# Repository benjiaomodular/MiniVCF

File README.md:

# MiniVCF

This is a diode-ladder voltage controlled low pass filter based on [Moritz Klein's diode ladder tutorial series](https://www.youtube.com/watch?v=jvNNgUl3al0).

More info on my website:  [https://benjiaomodular.com/post/2022-03-11-mini-vcf/](https://benjiaomodular.com/post/2022-03-11-mini-vcf/)

## Versions

### v1.1 - Quick fixes (Unverified)
- Fixed orientation of Cutoff and Post-LPF knobs.
- Updated toggle switch footprint to a bit more space.
- Swapped clipping LED positions. Positive clipping now at the top row.
- Added missing labels for OpAmps, adjusted some unreadable labels.

### v1.0 - Initial release
This is the first release of the module. I got it to work, but has a couple of issues.

#### Issues Encountered
- Cutoff and Post-LPF knobs are wired the opposite way.
- Holes for the toggle switch a bit too tight.

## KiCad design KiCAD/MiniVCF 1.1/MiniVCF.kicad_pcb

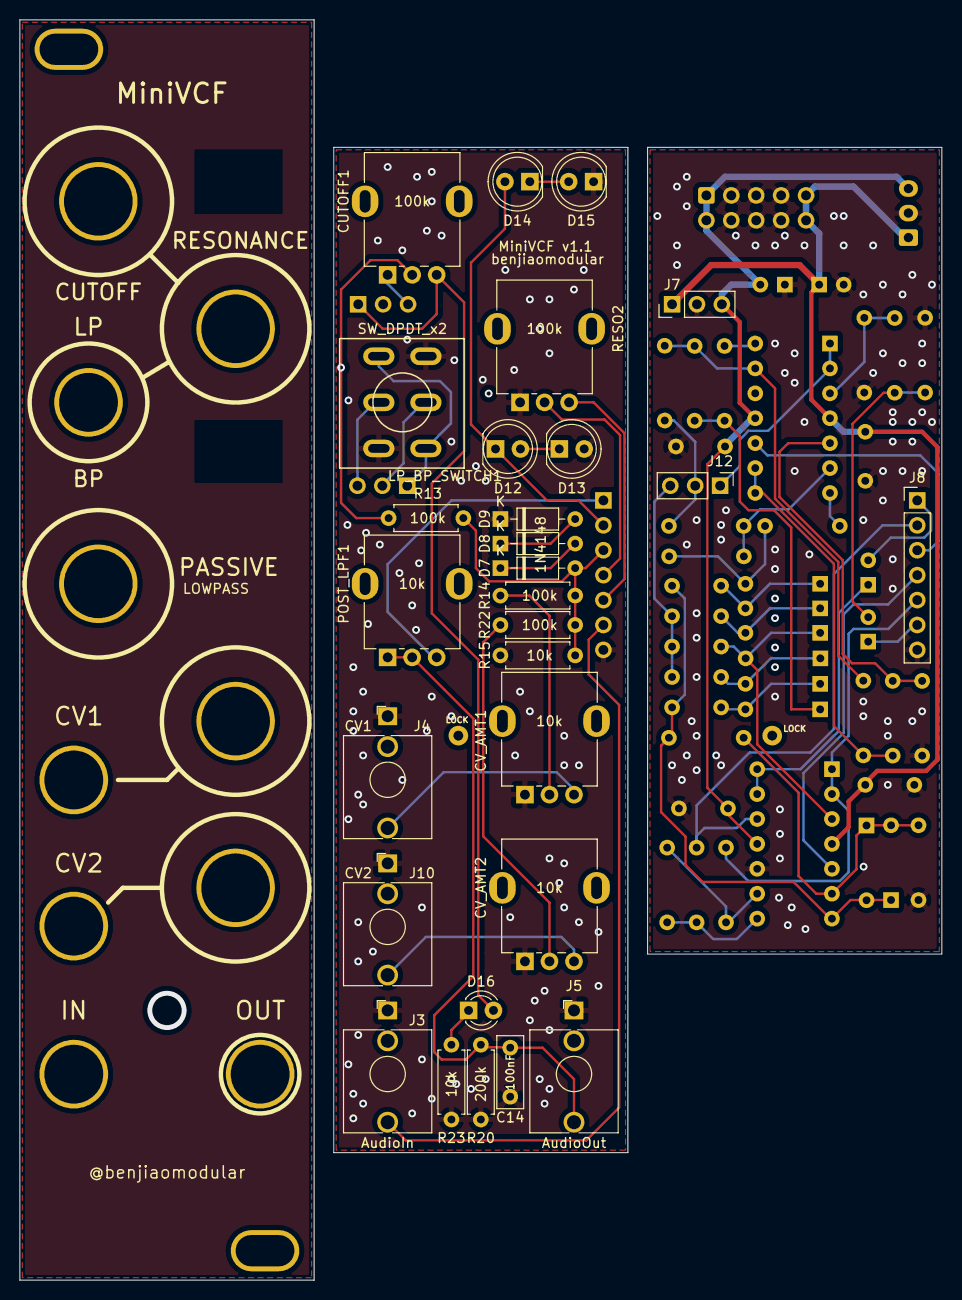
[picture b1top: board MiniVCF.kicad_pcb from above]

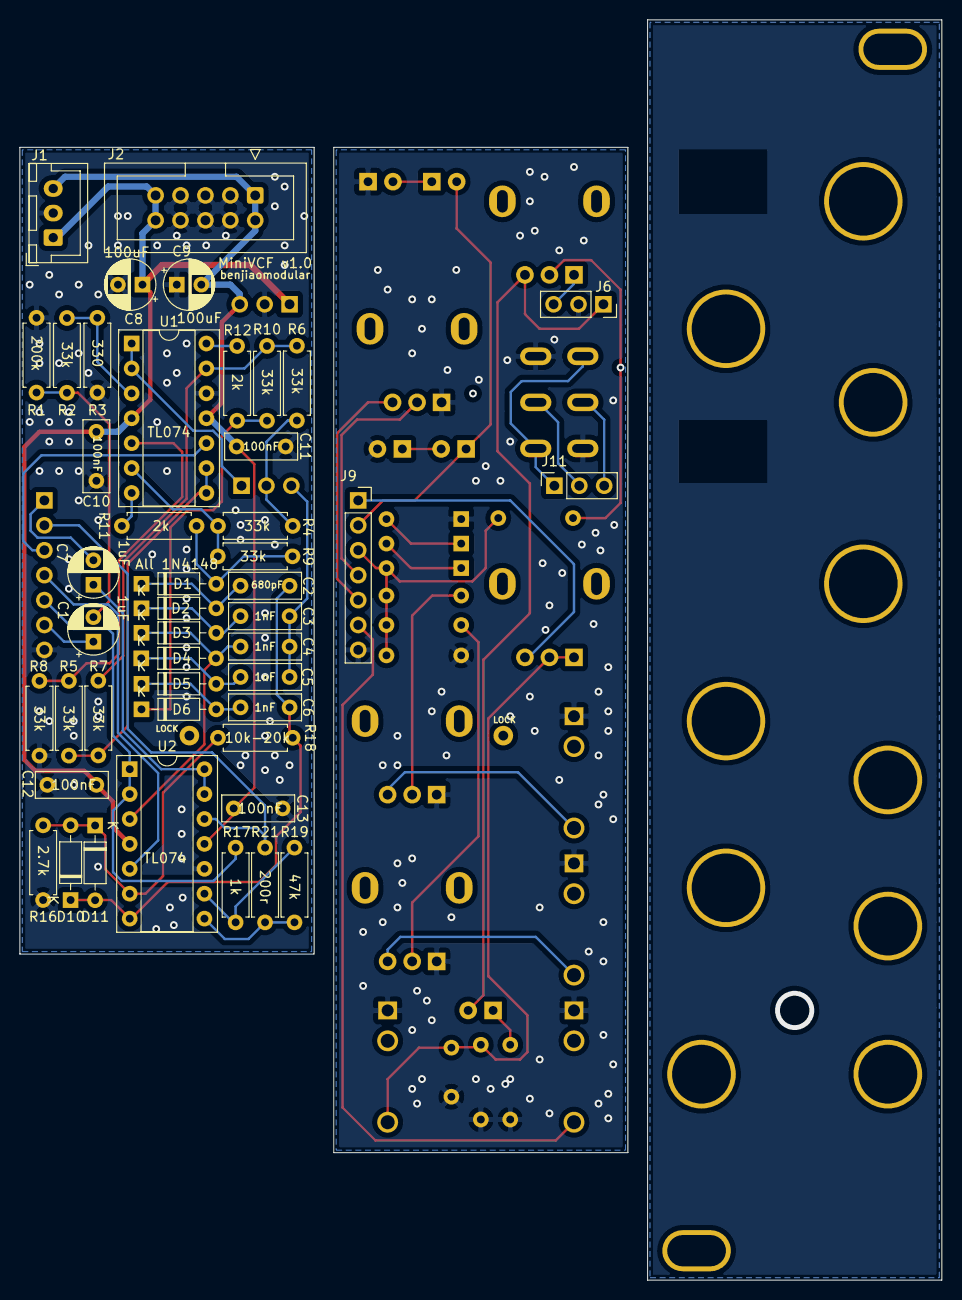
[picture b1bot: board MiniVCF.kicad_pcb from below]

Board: 2 copper layers, 94.0 x 128.5 mm, 73 parts (45 on the bottom side), 55 nets.

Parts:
C1, C7: 1uF; Capacitor_Radial_D5.0mm_P2.5mm
C2: 680pF; Capacitor_Rect_L7.2mm_W2.5mm_P5.00mm
C3, C4, C5, C6: 1nF; Capacitor_Rect_L7.2mm_W2.5mm_P5.00mm
C8, C9: 100uF; CP_Radial_D5.0mm_P2.50mm
C10, C11, C12, C13: 100nF; C_Rect_L7.2mm_W2.5mm_P5.00mm_FKS2_FKP2_MKS2_MKP2
C14: 100nF; Capacitor_Rect_L7.2mm_W2.5mm_P5.00mm
CUTOFF1: 100k; Potentiometer_RV09
CV_AMT1, CV_AMT2: 10k; Potentiometer_RV09
D1, D2, D3, D4, D5, D6, D7, D8, D9, D10, D11: 1N4148; D_DO-35_SOD27_P7.62mm_Horizontal
D12, D13, D14, D15: LED; LED_D5.0mm
D16: LED; LED_D3.0mm
J1: JST_BUS; JST_XH_B3B-XH-A_1x03_P2.50mm_Vertical
J2: IDC_BUS; IDC-Header_2x05_P2.54mm_Vertical
J3: AudioIn; AudioJack_3.5mm
J4: CV1; AudioJack_3.5mm
J5: AudioOut; AudioJack_3.5mm
J6: CONN_PWR1; PinSocket_1x03_P2.54mm_Vertical
J7: CONN_PWR2; PinHeader_1x03_P2.54mm_Vertical
J8: MAIN_BOARD_CONN; PinHeader_1x07_P2.54mm_Vertical
J9: CTRL_PANEL_CONN; PinSocket_1x07_P2.54mm_Vertical
J10: CV2; AudioJack_3.5mm
J11: CTRL_PANEL_CONN2; PinSocket_1x03_P2.54mm_Vertical
J12: MAIN_BOARD_CONN2; PinHeader_1x03_P2.54mm_Vertical
LP_BP_SWITCH1: SW_DPDT_x2; ToggleSwitch_MTS-202_DPDT
POST_LPF1: 10k; Potentiometer_RV09
R1, R20: 200k; Resistor_L6.3mm_D2.5mm_P7.62mm_Horizontal
R2, R4, R5, R6, R7, R8, R9, R10: 33k; Resistor_L6.3mm_D2.5mm_P7.62mm_Horizontal
R3: 330; Resistor_L6.3mm_D2.5mm_P7.62mm_Horizontal
R11, R12: 2k; Resistor_L6.3mm_D2.5mm_P7.62mm_Horizontal
R13, R14, R22: 100k; Resistor_L6.3mm_D2.5mm_P7.62mm_Horizontal
R15, R23: 10k; Resistor_L6.3mm_D2.5mm_P7.62mm_Horizontal
R16: 2.7k; Resistor_L6.3mm_D2.5mm_P7.62mm_Horizontal
R17: 1k; Resistor_L6.3mm_D2.5mm_P7.62mm_Horizontal
R18: 10k-20k; Resistor_L6.3mm_D2.5mm_P7.62mm_Horizontal
R19: 47k; Resistor_L6.3mm_D2.5mm_P7.62mm_Horizontal
R21: 200r; Resistor_L6.3mm_D2.5mm_P7.62mm_Horizontal
RESO2: 100k; Potentiometer_RV09
U1, U2: TL074; DIP-14_W7.62mm_Socket

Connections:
+12V: C8.1, C10.1, C12.1, J1.1, J2.9, J2.10, J7.1, U1.4, U2.4
-12V: C9.2, C11.2, C13.2, J1.3, J2.1, J2.2, J7.3, U1.11, U2.11
A_5: J9.5, RESO2.3
A_6: J9.4, RESO2.2
A_7: J11.2, LP_BP_SWITCH1.2
A_8: J11.1, LP_BP_SWITCH1.1, LP_BP_SWITCH1.6
A_9: J11.3, LP_BP_SWITCH1.5
A_AUDIO_IN: J3.T, J9.6
A_AUDIO_OUT: J9.1, POST_LPF1.3
A_CLIPPING_LEDS: D12.1, D14.2, J9.2
A_CV_IN: D7.2, J9.3, R13.2, R14.2, R15.2, R22.2
B_5: J8.5, R17.1, U2.1, U2.2
B_6: J8.4, U2.5
B_7: J12.2, R4.2, R6.1
B_8: J12.1, U1.1, U1.2
B_9: C3.2, C4.2, C5.2, J12.3
B_AUDIO_IN: C1.1, J8.6
B_AUDIO_OUT: C7.2, J8.1
B_CLIPPING_LEDS: J8.2, R21.1, U2.12
B_CV_IN: J8.3, U1.10
GND1: C14.1, CV_AMT1.1, CV_AMT2.1, D9.1, D13.2, D15.1, J3.S, J4.S, J5.S, J6.2, J9.7, J10.S, LP_BP_SWITCH1.3, LP_BP_SWITCH1.4, R15.1, R20.2, R23.2, RESO2.1
GND2: C8.2, C9.1, C10.2, C11.1, C12.2, C13.1, J1.2, J2.3, J2.4, J2.5, J2.6, J2.7, J2.8, J7.2, J8.7, R1.2, R3.1, R8.2, R16.1, U1.12, U2.10
NEG12V_1: CUTOFF1.1, J6.3
unnamed: C1.2, R1.1, R2.2
unnamed: C2.1, D1.1, D2.2
unnamed: C3.1, D2.1, D3.2
unnamed: C4.1, D3.1, D4.2, U2.3
unnamed: C5.1, D4.1, D5.2
unnamed: C6.1, D5.1, D6.2
unnamed: C7.1, U2.13, U2.14
unnamed: C14.2, J5.T, POST_LPF1.1, POST_LPF1.2, R20.1
unnamed: CUTOFF1.2, R13.1
unnamed: CV_AMT1.2, R14.1
unnamed: CV_AMT1.3, J4.T
unnamed: CV_AMT2.2, R22.1
unnamed: CV_AMT2.3, J10.T
unnamed: D1.2, R9.1, R11.2
unnamed: D6.1, R10.2, R12.2
unnamed: D7.1, D8.2
unnamed: D8.1, D9.2
unnamed: D10.2, D11.1, R16.2, R18.1, U2.6
unnamed: D12.2, D13.1
unnamed: D14.1, D15.2
unnamed: D16.1, R23.1
unnamed: R2.1, R3.2, U1.3
unnamed: R4.1, R9.2, U1.6
unnamed: R5.1, R8.1, U1.5
unnamed: R5.2, R7.1, U1.8, U1.9
unnamed: R6.2, R7.2, R10.1, U1.13
unnamed: R11.1, U1.7
unnamed: R12.1, U1.14
unnamed: R17.2, R19.1, U2.9
unnamed: R19.2, R21.2, U2.8
POS12V_1: CUTOFF1.3, D16.2, J6.1
RESO_FEEDBACK: C2.2, C6.2, D10.1, D11.2, R18.2, U2.7

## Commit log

2022-01-23 Added description
2022-02-05 First pcb layout draft
2022-02-06 Fixed toggle switch connections
2022-02-07 Added fab files for v1.0
2022-02-07 Fixed fab files
2022-02-07 Added a lock hole on control and main board
2022-02-19 Added v1.1 with initial fixes
2022-02-19 Updated version number
2022-02-19 Adjusted unreadable cap label
2022-02-19 Updated changelog
2022-03-10 added schematics export
2022-03-11 Added link to my website
2022-03-11 Added files for v1.1
2022-03-13 Added fab files for v1.1
